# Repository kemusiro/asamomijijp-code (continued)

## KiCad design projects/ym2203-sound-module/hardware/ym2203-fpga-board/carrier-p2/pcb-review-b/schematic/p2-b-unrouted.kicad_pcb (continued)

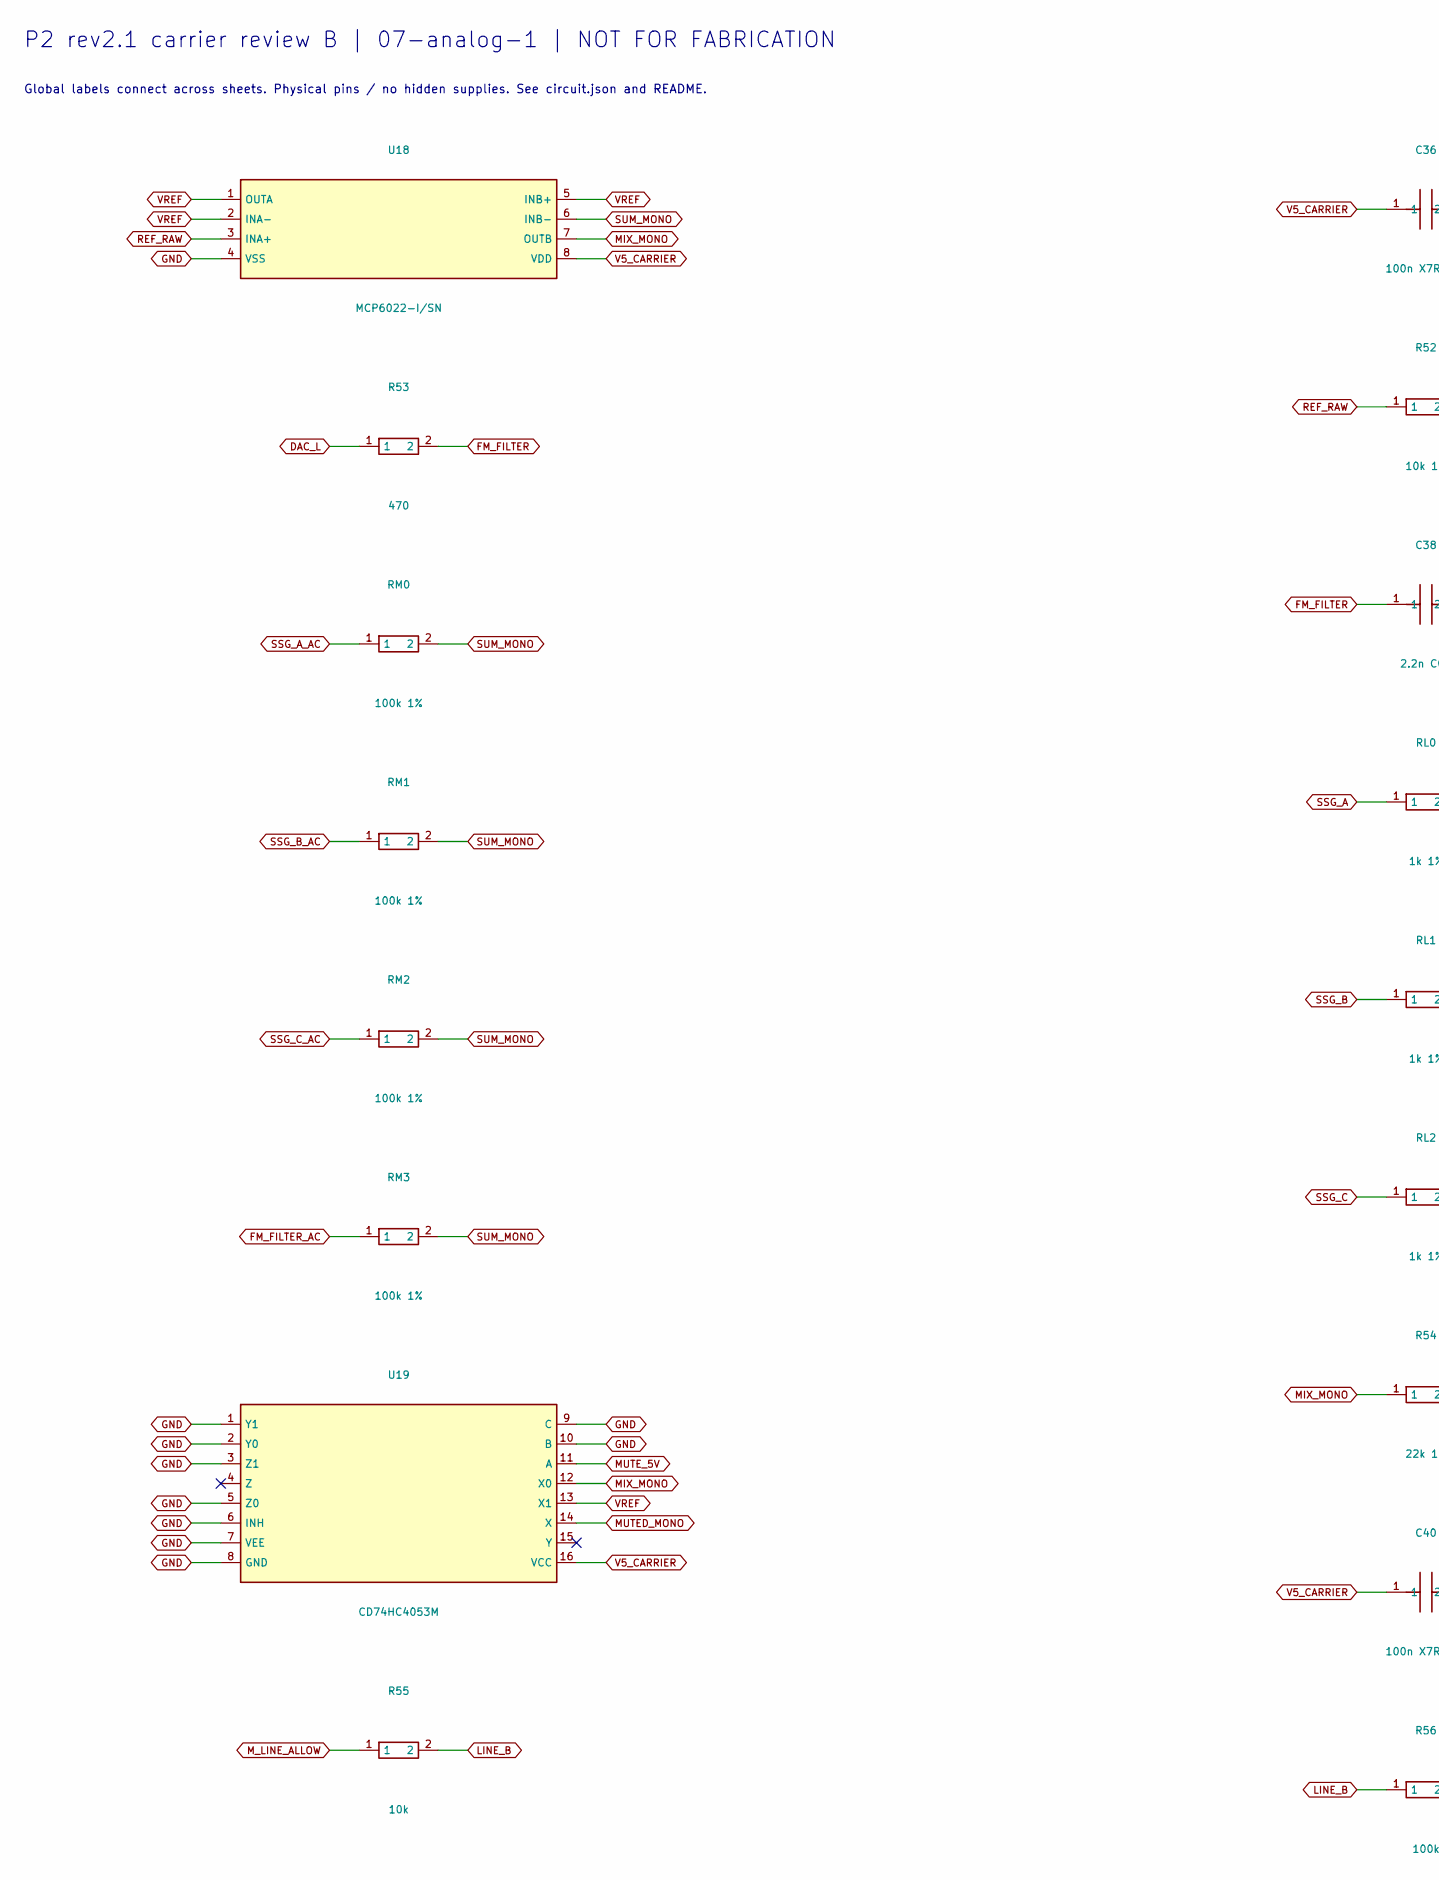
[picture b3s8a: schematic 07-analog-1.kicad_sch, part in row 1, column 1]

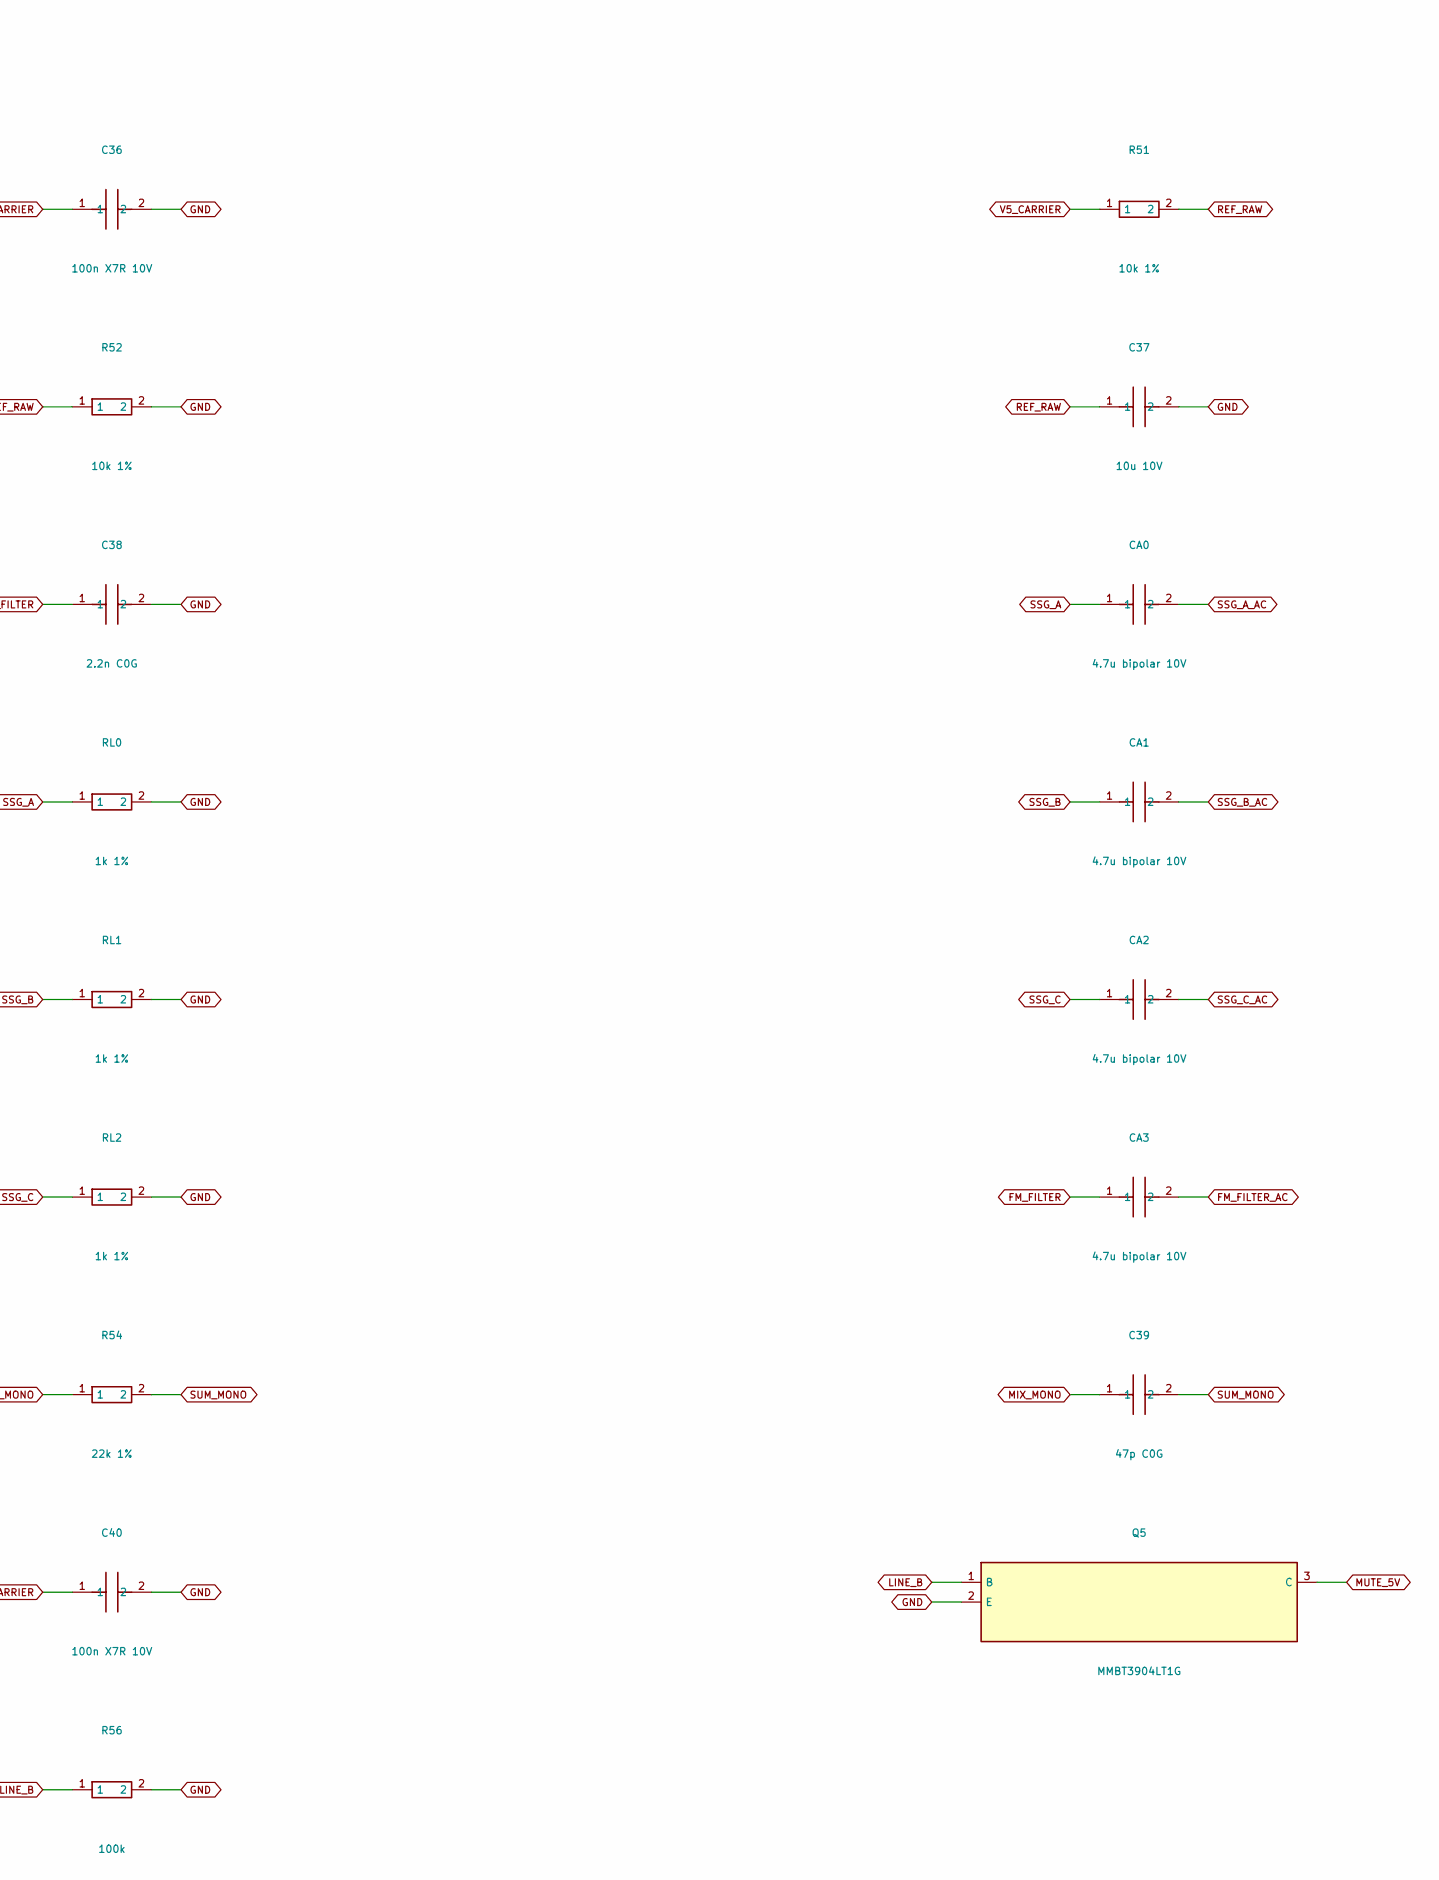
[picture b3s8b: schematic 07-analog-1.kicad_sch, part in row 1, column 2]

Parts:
C36, C40: 100n X7R 10V; C_0805_2012Metric
C37: 10u 10V; C_0805_2012Metric
C38: 2.2n C0G; C_0805_2012Metric
C39: 47p C0G; C_0805_2012Metric
CA0, CA1, CA2, CA3: 4.7u bipolar 10V; C_Radial_D5.0mm_H11.0mm_P2.00mm
Q5: MMBT3904LT1G; SOT-23
R51, R52: 10k 1%; R_0805_2012Metric
R53: 470; R_0805_2012Metric
R54: 22k 1%; R_0805_2012Metric
R55: 10k; R_0805_2012Metric
R56: 100k; R_0805_2012Metric
RL0, RL1, RL2: 1k 1%; R_0805_2012Metric
RM0, RM1, RM2, RM3: 100k 1%; R_0805_2012Metric
U18: MCP6022-I/SN; SOIC-8_3.9x4.9mm_P1.27mm
U19: CD74HC4053M; SOIC-16_3.9x9.9mm_P1.27mm

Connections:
DAC_L: R53.1; also elsewhere on the board
FM_FILTER: C38.1, CA3.1, R53.2
FM_FILTER_AC: CA3.2, RM3.1
GND: C36.2, C37.2, C38.2, C40.2, Q5.2 (E), R52.2, R56.2, RL0.2, RL1.2, RL2.2, U18.4 (VSS), U19.1 (Y1), U19.2 (Y0), U19.3 (Z1), U19.5 (Z0), U19.6 (INH), U19.7 (VEE), U19.8 (GND), U19.9 (C), U19.10 (B); also elsewhere on the board
LINE_B: Q5.1 (B), R55.2, R56.1
MIX_MONO: C39.1, R54.1, U18.7 (OUTB), U19.12 (X0)
MUTED_MONO: U19.14 (X); also elsewhere on the board
MUTE_5V: Q5.3 (C), U19.11 (A); also elsewhere on the board
M_LINE_ALLOW: R55.1; also elsewhere on the board
REF_RAW: C37.1, R51.2, R52.1, U18.3 (INA+)
SSG_A: CA0.1, RL0.1; also elsewhere on the board
SSG_A_AC: CA0.2, RM0.1
SSG_B: CA1.1, RL1.1; also elsewhere on the board
SSG_B_AC: CA1.2, RM1.1
SSG_C: CA2.1, RL2.1; also elsewhere on the board
SSG_C_AC: CA2.2, RM2.1
SUM_MONO: C39.2, R54.2, RM0.2, RM1.2, RM2.2, RM3.2, U18.6 (INB-)
V5_CARRIER: C36.1, C40.1, R51.1, U18.8 (VDD), U19.16 (VCC); also elsewhere on the board
VREF: U18.1 (OUTA), U18.2 (INA-), U18.5 (INB+), U19.13 (X1)

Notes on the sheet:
P2 rev2.1 carrier review B | 07-analog-1 | NOT FOR FABRICATION
Global labels connect across sheets. Physical pins / no hidden supplies. See circuit.json and README.

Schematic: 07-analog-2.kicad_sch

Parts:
C41: 4.7u bipolar 10V; C_Radial_D5.0mm_H11.0mm_P2.00mm
JLINE: JLINE; PinHeader_1x03_P2.54mm_Vertical
JPOT: JPOT; PinHeader_1x06_P2.54mm_Vertical
R57: 10k; R_0805_2012Metric
R58: 100k; R_0805_2012Metric
R59, R60: 100; R_0805_2012Metric

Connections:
GND: JLINE.2, JPOT.1, JPOT.4, R58.2; also elsewhere on the board
LINE_L: JLINE.1, R59.2
LINE_R: JLINE.3, R60.2
MUTED_MONO: C41.1; also elsewhere on the board
MUTE_5V: R57.2; also elsewhere on the board
OUT_AC: C41.2, JPOT.3, JPOT.6, R58.1
V5_CARRIER: R57.1; also elsewhere on the board
VOL_L: JPOT.2, R59.1
VOL_R: JPOT.5, R60.1

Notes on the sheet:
P2 rev2.1 carrier review B | 07-analog-2 | NOT FOR FABRICATION
Global labels connect across sheets. Physical pins / no hidden supplies. See circuit.json and README.

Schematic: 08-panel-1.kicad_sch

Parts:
CPANEL: 100n X7R 10V; C_0805_2012Metric
DLED0: RX GREEN; LED_D3.0mm
DLED1: FM1; LED_D3.0mm
DLED2: FM2; LED_D3.0mm
DLED3: FM3; LED_D3.0mm
DLED4: SSGA; LED_D3.0mm
DLED5: SSGB; LED_D3.0mm
RLED0, RLED1, RLED2, RLED3, RLED4, RLED5, RLED6: 1k; R_0805_2012Metric
RP0, RP1, RP2, RP3, RP4, RP5: 10k; R_0805_2012Metric
SWCLOCK: 4-bit DIP ON=0 SW1=LSB; SW_DIP_SPSTx04_Slide_6.7x11.72mm_W7.62mm_P2.54mm_LowProfile
SWSTOP: STOP; SW_PUSH_6mm_H4.3mm
SWTEST: TEST; SW_PUSH_6mm_H4.3mm
UPANEL: MCP23017-E/SO; SOIC-28W_7.5x17.9mm_P1.27mm

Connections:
DIP1_N: RP0.2, SWCLOCK.1 (SW1), UPANEL.21 (GPA0)
DIP2_N: RP1.2, SWCLOCK.2 (SW2), UPANEL.22 (GPA1)
DIP3_N: RP2.2, SWCLOCK.3 (SW3), UPANEL.23 (GPA2)
DIP4_N: RP3.2, SWCLOCK.4 (SW4), UPANEL.24 (GPA3)
FM1_LED_N: DLED1.1 (K), UPANEL.1 (GPB0)
FM2_LED_N: DLED2.1 (K), UPANEL.2 (GPB1)
FM3_LED_N: DLED3.1 (K), UPANEL.3 (GPB2)
GND: CPANEL.2, SWCLOCK.5 (GND), SWCLOCK.6 (GND), SWCLOCK.7 (GND), SWCLOCK.8 (GND), SWSTOP.2 (B), SWTEST.2 (B), UPANEL.10 (VSS), UPANEL.15 (A0), UPANEL.16 (A1), UPANEL.17 (A2); also elsewhere on the board
LED_ANODE0: DLED0.2 (A), RLED0.1
LED_ANODE1: DLED1.2 (A), RLED1.1
LED_ANODE2: DLED2.2 (A), RLED2.1
LED_ANODE3: DLED3.2 (A), RLED3.1
LED_ANODE4: DLED4.2 (A), RLED4.1
LED_ANODE5: DLED5.2 (A), RLED5.1
LED_ANODE6: RLED6.1; also elsewhere on the board
PANEL_SCL: UPANEL.12 (SCL); also elsewhere on the board
PANEL_SDA: UPANEL.13 (SDA); also elsewhere on the board
RUN_N: UPANEL.18 (RESETn); also elsewhere on the board
RX_LED_N: DLED0.1 (K), UPANEL.28 (GPA7)
SSGA_LED_N: DLED4.1 (K), UPANEL.4 (GPB3)
SSGB_LED_N: DLED5.1 (K), UPANEL.5 (GPB4)
SSGC_LED_N: UPANEL.6 (GPB5); also elsewhere on the board
STOP_N: RP4.2, SWSTOP.1 (A), UPANEL.25 (GPA4)
TEST_N: RP5.2, SWTEST.1 (A), UPANEL.26 (GPA5)
V3V3: CPANEL.1, RLED0.2, RLED1.2, RLED2.2, RLED3.2, RLED4.2, RLED5.2, RLED6.2, RP0.1, RP1.1, RP2.1, RP3.1, RP4.1, RP5.1, UPANEL.9 (VDD); also elsewhere on the board

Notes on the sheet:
P2 rev2.1 carrier review B | 08-panel-1 | NOT FOR FABRICATION
Global labels connect across sheets. Physical pins / no hidden supplies. See circuit.json and README.

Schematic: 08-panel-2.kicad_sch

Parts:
DLED6: SSGC; LED_D3.0mm

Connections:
LED_ANODE6: DLED6.2 (A); also elsewhere on the board
SSGC_LED_N: DLED6.1 (K); also elsewhere on the board

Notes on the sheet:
P2 rev2.1 carrier review B | 08-panel-2 | NOT FOR FABRICATION
Global labels connect across sheets. Physical pins / no hidden supplies. See circuit.json and README.

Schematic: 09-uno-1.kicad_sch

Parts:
JP5V: OPEN DEFAULT / SHIELD POWER; SolderJumper-2_P1.3mm_Open_RoundedPad1.0x1.5mm
JP_SCL: CLOSED I2C / OPEN ADC (STOPPED); SolderJumper-2_P1.3mm_Bridged_RoundedPad1.0x1.5mm
JP_SDA: CLOSED I2C / OPEN ADC (STOPPED); SolderJumper-2_P1.3mm_Bridged_RoundedPad1.0x1.5mm
JUNO_A: JUNO_A 3V3 ONLY; JUNO_A
JUNO_D0: JUNO_D0 3V3 ONLY; JUNO_D0
JUNO_D8: JUNO_D8 3V3 ONLY; JUNO_D8
JUNO_PWR: JUNO_PWR 3V3 ONLY; JUNO_PWR
JUNO_SPI: JUNO_SPI 3V3 ONLY; JUNO_SPI

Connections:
EXT_A0: JUNO_A.1 (A0); also elsewhere on the board
EXT_A1: JUNO_A.2 (A1); also elsewhere on the board
EXT_A2: JUNO_A.3 (A2); also elsewhere on the board
EXT_A3: JUNO_A.4 (A3); also elsewhere on the board
EXT_A4: JP_SDA.1 (MCU_HEADER), JUNO_A.5 (A4), JUNO_D8.9 (SDA); also elsewhere on the board
EXT_A5: JP_SCL.1 (MCU_HEADER), JUNO_A.6 (A5), JUNO_D8.10 (SCL); also elsewhere on the board
EXT_D0: JUNO_D0.1 (D0); also elsewhere on the board
EXT_D1: JUNO_D0.2 (D1); also elsewhere on the board
EXT_D2: JUNO_D0.3 (D2); also elsewhere on the board
EXT_D3: JUNO_D0.4 (D3); also elsewhere on the board
EXT_D4: JUNO_D0.5 (D4); also elsewhere on the board
EXT_D5: JUNO_D0.6 (D5); also elsewhere on the board
EXT_D6: JUNO_D0.7 (D6); also elsewhere on the board
EXT_D7: JUNO_D0.8 (D7); also elsewhere on the board
EXT_D8: JUNO_D8.1 (D8); also elsewhere on the board
EXT_D9: JUNO_D8.2 (D9); also elsewhere on the board
EXT_D10: JUNO_D8.3 (D10); also elsewhere on the board
EXT_D11: JUNO_D8.4 (D11), JUNO_SPI.4 (COPI); also elsewhere on the board
EXT_D12: JUNO_D8.5 (D12), JUNO_SPI.1 (CIPO); also elsewhere on the board
EXT_D13: JUNO_D8.6 (D13), JUNO_SPI.3 (SCK); also elsewhere on the board
GND: JUNO_D8.7 (GND), JUNO_PWR.6 (GND), JUNO_PWR.7 (GND), JUNO_SPI.6 (GND); also elsewhere on the board
PANEL_SCL: JP_SCL.2 (BOARD_I2C); also elsewhere on the board
PANEL_SDA: JP_SDA.2 (BOARD_I2C); also elsewhere on the board
RUN_N: JUNO_PWR.3 (RESET), JUNO_SPI.5 (RESET); also elsewhere on the board
SHIELD_5V: JP5V.2 (SHIELD), JUNO_PWR.5 (5V)
V3V3: JUNO_PWR.2 (IOREF), JUNO_SPI.2 (VCC_3V3); also elsewhere on the board
V3_AUX: JUNO_PWR.4 (3V3); also elsewhere on the board
V5_CARRIER: JP5V.1 (5V); also elsewhere on the board

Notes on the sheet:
P2 rev2.1 carrier review B | 09-uno-1 | NOT FOR FABRICATION
Global labels connect across sheets. Physical pins / no hidden supplies. See circuit.json and README.

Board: 4 copper layers, 172 parts (0 on the bottom side), 137 nets, no tracks yet.

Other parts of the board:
H1, H2, H3, H4, H5, H6, H7, H8: MountingHole_3.2mm_M3

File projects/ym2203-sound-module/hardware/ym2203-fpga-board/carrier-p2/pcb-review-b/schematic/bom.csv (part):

Reference,Value,Footprint,Sheet,Datasheet,Review note
MPGA,PGA2350 PIM722 SOCKET,P2C:PGA2350_Socket_64,01-module,https://shop.pimoroni.com/products/pga2350,Top view A1 at upper left. GP47 B8 NC: PSRAM onboard. USB 27R4 ALREADY on module. ADC_VREF/3V3_EN NC.
JHOST,JHOST,Connector_PinHeader_2.54mm:PinHeader_1x04_P2.54mm_Vertical,01-module,,Existing OTHER Pico GP0 SDA / GP1 SCL; 100kHz / 0x42; NO supply pin
JSWD,JSWD,Connector_PinHeader_2.54mm:PinHeader_1x03_P2.54mm_Vertical,01-module,,3.3V SWD probe; never power carrier through probe
SWRESET,RESET,Button_Switch_THT:SW_PUSH_6mm_H4.3mm,01-module,,Two contact numbers; each has two duplicated physical pads in KiCad footprint
SWBOOT,BOOTSEL,Button_Switch_THT:SW_PUSH_6mm_H4.3mm,01-module,,Two contact numbers; each has two duplicated physical pads in KiCad footprint
RRUN,10k,Resistor_SMD:R_0805_2012Metric,01-module,,
CRUN,1n C0G,Capacitor_SMD:C_0805_2012Metric,01-module,,Capacitor body/height and effective capacitance to be checked against final MPN
JPOWER,JPOWER,Connector_PinHeader_2.54mm:PinHeader_1x02_P2.54mm_Vertical,02-power-usb,,Regulated external5V; 1.5A supply target; verify 4.95..5.05V at YM under load
F1,PTC 1.1A hold,Fuse:Fuse_1812_4532Metric,02-power-usb,,
C1,100u 10V,Capacitor_THT:CP_Radial_D6.3mm_P2.50mm,02-power-usb,,Capacitor body/height and effective capacitance to be checked against final MPN
C2,10u 10V,Capacitor_SMD:C_0805_2012Metric,02-power-usb,,Capacitor body/height and effective capacitance to be checked against final MPN
JUSB,HRO TYPE-C-31-M-12 USB2 DEVICE,Connector_USB:USB_C_Receptacle_HRO_TYPE-C-31-M-12,02-power-usb,http://www.krhro.com/uploads/soft/180320/1-1P320120243.pdf,Self-powered. A6/B6 DP; A7/B7 DM; SBU NC. Verify exact purchased connector drawing before layout release.
RCC1,5.1k 1%,Resistor_SMD:R_0805_2012Metric,02-power-usb,,
RCC2,5.1k 1%,Resistor_SMD:R_0805_2012Metric,02-power-usb,,
UESD,USBLC6-2SC6,Package_TO_SOT_SMD:SOT-23-6,02-power-usb,https://www.st.com/resource/en/datasheet/usblc6-2.pdf,"Place at USB connector, short return. VBUS protection/sense only; no external5V power path."
CVBUS,100n X7R 10V,Capacitor_SMD:C_0805_2012Metric,02-power-usb,,Capacitor body/height and effective capacitance to be checked against final MPN
RVB1,47k 0.1%,Resistor_SMD:R_0805_2012Metric,02-power-usb,,
RVB2,68k 0.1%,Resistor_SMD:R_0805_2012Metric,02-power-usb,,
CVBD,100p C0G,Capacitor_SMD:C_0805_2012Metric,02-power-usb,,Capacitor body/height and effective capacitance to be checked against final MPN
UVBUS,SN74LVC1G17DBVR,Package_TO_SOT_SMD:SOT-23-5,02-power-usb,https://www.ti.com/lit/ds/symlink/sn74lvc1g17.pdf,Schmitt buffer / Ioff; USB VBUS sense to GP46; no power through USB
CVB3,100n X7R 10V,Capacitor_SMD:C_0805_2012Metric,02-power-usb,,Capacitor body/height and effective capacitance to be checked against final MPN
RVB3,100k,Resistor_SMD:R_0805_2012Metric,02-power-usb,,
Q1,MMBT3904LT1G,Package_TO_SOT_SMD:SOT-23,03-default-stop,https://www.onsemi.com/pdf/datasheet/mmbt3904lt1-d.pdf,
R19,4.7k,Resistor_SMD:R_0805_2012Metric,03-default-stop,,
Q2,MMBT3904LT1G,Package_TO_SOT_SMD:SOT-23,03-default-stop,https://www.onsemi.com/pdf/datasheet/mmbt3904lt1-d.pdf,
R20,10k,Resistor_SMD:R_0805_2012Metric,03-default-stop,,
R21,100k,Resistor_SMD:R_0805_2012Metric,03-default-stop,,
R22,10k,Resistor_SMD:R_0805_2012Metric,03-default-stop,,
R23,100k,Resistor_SMD:R_0805_2012Metric,03-default-stop,,
RPDAC,10k,Resistor_SMD:R_0805_2012Metric,03-default-stop,,
RPLINE,10k,Resistor_SMD:R_0805_2012Metric,03-default-stop,,
U8,SN74LVC8T245PWR,Package_SO:TSSOP-24_4.4x7.8mm_P0.65mm,04-ym-bus,https://www.ti.com/lit/ds/symlink/sn74lvc8t245.pdf,Bare IC pinout: OE=22 DIR=2; NOT the Rev C breakout numbering
U9,SN74LVC8T245PWR,Package_SO:TSSOP-24_4.4x7.8mm_P0.65mm,04-ym-bus,https://www.ti.com/lit/ds/symlink/sn74lvc8t245.pdf,Bare IC pinout: OE=22 DIR=2; NOT the Rev C breakout numbering
C11,100n X7R 10V,Capacitor_SMD:C_0805_2012Metric,04-ym-bus,,Capacitor body/height and effective capacitance to be checked against final MPN
C12,100n X7R 10V,Capacitor_SMD:C_0805_2012Metric,04-ym-bus,,Capacitor body/height and effective capacitance to be checked against final MPN
C13,100n X7R 10V,Capacitor_SMD:C_0805_2012Metric,04-ym-bus,,Capacitor body/height and effective capacitance to be checked against final MPN
C14,100n X7R 10V,Capacitor_SMD:C_0805_2012Metric,04-ym-bus,,Capacitor body/height and effective capacitance to be checked against final MPN
C15,100n X7R 10V,Capacitor_SMD:C_0805_2012Metric,04-ym-bus,,Capacitor body/height and effective capacitance to be checked against final MPN
C16,100n X7R 10V,Capacitor_SMD:C_0805_2012Metric,04-ym-bus,,Capacitor body/height and effective capacitance to be checked against final MPN
RDIR,10k,Resistor_SMD:R_0805_2012Metric,04-ym-bus,,
RDOE,10k,Resistor_SMD:R_0805_2012Metric,04-ym-bus,,
RCOE,10k,Resistor_SMD:R_0805_2012Metric,04-ym-bus,,
RD0,100k,Resistor_SMD:R_0805_2012Metric,04-ym-bus,,
RD1,100k,Resistor_SMD:R_0805_2012Metric,04-ym-bus,,
RD2,100k,Resistor_SMD:R_0805_2012Metric,04-ym-bus,,
RD3,100k,Resistor_SMD:R_0805_2012Metric,04-ym-bus,,
RD4,100k,Resistor_SMD:R_0805_2012Metric,04-ym-bus,,
RD5,100k,Resistor_SMD:R_0805_2012Metric,04-ym-bus,,
RD6,100k,Resistor_SMD:R_0805_2012Metric,04-ym-bus,,
RD7,100k,Resistor_SMD:R_0805_2012Metric,04-ym-bus,,
R32,10k,Resistor_SMD:R_0805_2012Metric,04-ym-bus,,
RMC32,10k,Resistor_SMD:R_0805_2012Metric,04-ym-bus,,
R33,10k,Resistor_SMD:R_0805_2012Metric,04-ym-bus,,
RMC33,10k,Resistor_SMD:R_0805_2012Metric,04-ym-bus,,
R34,10k,Resistor_SMD:R_0805_2012Metric,04-ym-bus,,
RMC34,10k,Resistor_SMD:R_0805_2012Metric,04-ym-bus,,
R35,100k,Resistor_SMD:R_0805_2012Metric,04-ym-bus,,
RMA,100k,Resistor_SMD:R_0805_2012Metric,04-ym-bus,,
U12,YM2203C SOCKET,Package_DIP:DIP-40_W15.24mm_Socket,05-clock-ym,https://www.bitsavers.org/components/yamaha/YM2203_198911.pdf,IO ports A/B unused; IRQ unconnected; 5V supply
C19,100n X7R 10V,Capacitor_SMD:C_0805_2012Metric,05-clock-ym,,Capacitor body/height and effective capacitance to be checked against final MPN
C20,10u 10V,Capacitor_SMD:C_0805_2012Metric,05-clock-ym,,Capacitor body/height and effective capacitance to be checked against final MPN
U13,Si5351A-B-GT,Package_SO:MSOP-10_3x3mm_P0.5mm,05-clock-ym,https://www.skyworksinc.com/-/media/SkyWorks/SL/documents/pu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,Blank no-boot preset; P2 firmware must disable CLK1/2 and configure CLK0 before reset release
Y1,25MHz CL10pF +/-20ppm,Crystal:Crystal_SMD_3225-4Pin_3.2x2.5mm,05-clock-ym,,ABM8-25.000MHZ-10-1-U-T candidate; ESR/drive and actual footprint need confirmation
C21,100n X7R 10V,Capacitor_SMD:C_0805_2012Metric,05-clock-ym,,Capacitor body/height and effective capacitance to be checked against final MPN
C22,100n X7R 10V,Capacitor_SMD:C_0805_2012Metric,05-clock-ym,,Capacitor body/height and effective capacitance to be checked against final MPN
R37,2.2k,Resistor_SMD:R_0805_2012Metric,05-clock-ym,,
R38,2.2k,Resistor_SMD:R_0805_2012Metric,05-clock-ym,,
U14,SN74LVC1T45DBVR,Package_TO_SOT_SMD:SOT-23-6,05-clock-ym,https://www.ti.com/lit/ds/symlink/sn74lvc1t45.pdf,Fixed A->B; clock may run while YM RESET is asserted
C23,100n X7R 10V,Capacitor_SMD:C_0805_2012Metric,05-clock-ym,,Capacitor body/height and effective capacitance to be checked against final MPN
C24,100n X7R 10V,Capacitor_SMD:C_0805_2012Metric,05-clock-ym,,Capacitor body/height and effective capacitance to be checked against final MPN
R39,33,Resistor_SMD:R_0805_2012Metric,05-clock-ym,,
R40,100k,Resistor_SMD:R_0805_2012Metric,05-clock-ym,,
U16,SN74LVC125APWR,Package_SO:TSSOP-14_4.4x5mm_P0.65mm,06-dac,https://www.ti.com/lit/ds/symlink/sn74lvc125a.pdf,
C27,100n X7R 10V,Capacitor_SMD:C_0805_2012Metric,06-dac,,Capacitor body/height and effective capacitance to be checked against final MPN
R42,100k,Resistor_SMD:R_0805_2012Metric,06-dac,,
R43,100k,Resistor_SMD:R_0805_2012Metric,06-dac,,
R44,100k,Resistor_SMD:R_0805_2012Metric,06-dac,,
R45,2.2k,Resistor_SMD:R_0805_2012Metric,06-dac,,
R46,2.2k,Resistor_SMD:R_0805_2012Metric,06-dac,,
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
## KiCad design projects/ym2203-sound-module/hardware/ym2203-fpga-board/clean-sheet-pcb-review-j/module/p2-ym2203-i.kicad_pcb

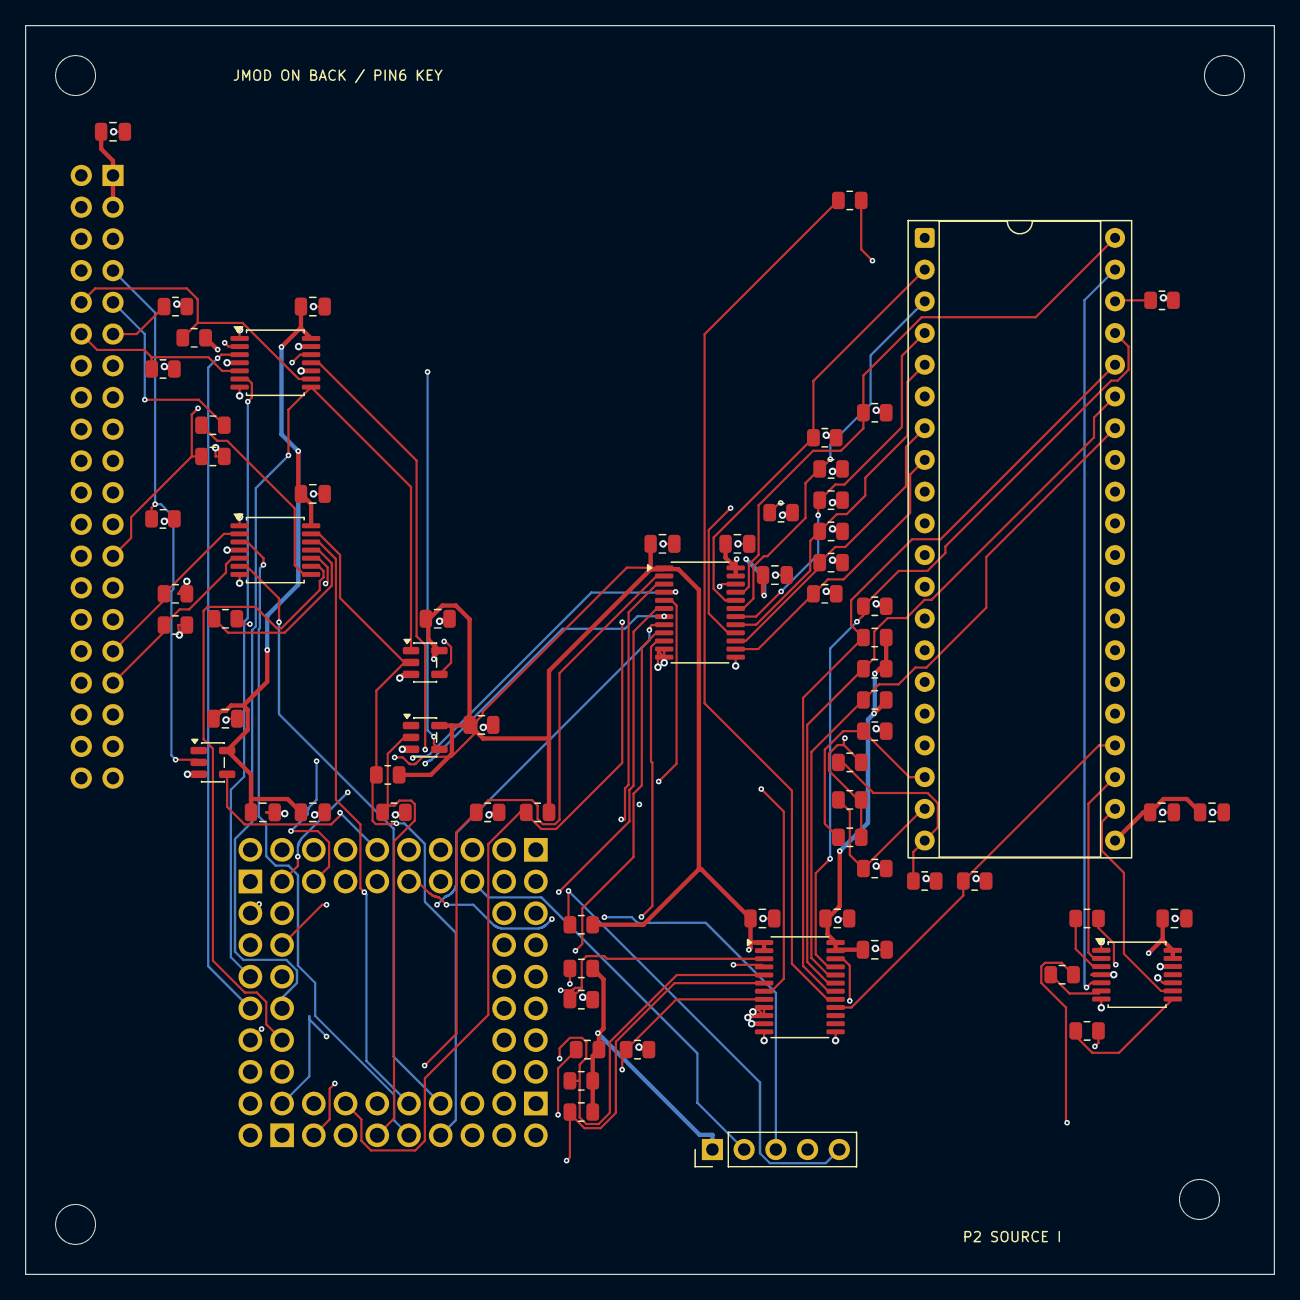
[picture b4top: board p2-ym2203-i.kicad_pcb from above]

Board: 4 copper layers, 100.0 x 100.0 mm, 80 parts (1 on the bottom side), 73 nets.

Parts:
C11, C12, C13, C14, C15, C16, C19, C27: 100n X7R 10V; C_0805_2012Metric
C20: 10u 10V; C_0805_2012Metric
CCORE: 100n X7R 10V; C_0805_2012Metric
CCOREB: 4.7u X7R 10V; C_0805_2012Metric
CMOD5: 22u X7R 10V; C_0805_2012Metric
CUALERT: 100n X7R 10V; C_0805_2012Metric
CULINK0, CULINK1: 100n X7R 10V; C_0805_2012Metric
CURUNOD: 100n X7R 10V; C_0805_2012Metric
CUTXOR: 100n X7R 10V; C_0805_2012Metric
H1, H2, H3, H4: MountingHole_3.2mm_M3
JCORE1: Core2350B0 P1 / individual receptacles; Core2350B0_P1_IndividualSockets
JCORE2: Core2350B0 P2 / individual receptacles; Core2350B0_P2_IndividualSockets
JCORE3: Core2350B0 P3 / individual receptacles; Core2350B0_P3_IndividualSockets
JCORE4: Core2350B0 P4 / individual receptacles; Core2350B0_P4_IndividualSockets
JMOD: P2 G40 / KEY6 / NO LEGACY MATE; PinHeader_2x20_P2.54mm_Vertical
JSWD: Core SWD / VREF sense only; PinHeader_1x05_P2.54mm_Vertical
R32, R33, R34: 10k; R_0805_2012Metric
R35, R40: 100k; R_0805_2012Metric
R39: 33; R_0805_2012Metric
RCOE: 10k; R_0805_2012Metric
RD0, RD1, RD2, RD3, RD4, RD5, RD6, RD7: 100k; R_0805_2012Metric
RDIR: 10k; R_0805_2012Metric
RDOE: 10k; R_0805_2012Metric
RENPD: 10k; R_0805_2012Metric
RL0, RL1, RL2: 1.33k 1%; R_0805_2012Metric
RMA: 100k; R_0805_2012Metric
RMADR: 100k; R_0805_2012Metric
RMBCK: 100k; R_0805_2012Metric
RMC32, RMC33, RMC34: 10k; R_0805_2012Metric
RMCLK: 100k; R_0805_2012Metric
RMCS: 10k; R_0805_2012Metric
RMLR: 100k; R_0805_2012Metric
RMMOSI: 100k; R_0805_2012Metric
RMSCK: 100k; R_0805_2012Metric
RMTXDATA: 33; R_0805_2012Metric
RMTXMISO: 33; R_0805_2012Metric
RRELDEFAULT: 100k; R_0805_2012Metric
RRUNUP: 10k; R_0805_2012Metric
RS3, RS6, RS8: 33; R_0805_2012Metric
RSMIXA: 10k 1%; R_0805_2012Metric
RSMIXB: 10k 1%; R_0805_2012Metric
RSMIXC: 10k 1%; R_0805_2012Metric
RTXDIS: 10k; R_0805_2012Metric
RYMRESET: 10k; R_0805_2012Metric
U8, U9: SN74LVC8T245PWR; TSSOP-24_4.4x7.8mm_P0.65mm
U12: YM2203C SOCKET; DIP-40_W15.24mm_Socket
U16: SN74LV4T125PWR; TSSOP-14_4.4x5mm_P0.65mm
UALERT: SN74LVC1G07DBVR; SOT-23-5
ULINK0, ULINK1: SN74LV4T125PWR; TSSOP-14_4.4x5mm_P0.65mm
URUNOD: SN74LVC1G07DBVR; SOT-23-5
UTXOR: SN74LVC1G32DBVR; SOT-23-5

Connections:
AUDIO_L: JMOD.37, RSMIXA.2, RSMIXB.2, RSMIXC.2
BUF_M_FM_CLK: RS6.1, U16.6
BUF_M_FM_SD: RS3.1, U16.3
BUF_M_FM_SH: RS8.1, U16.8
CORE_RUN_N: JCORE2.11, JSWD.5, RRUNUP.1, URUNOD.4
CORE_SWCLK: JCORE2.10, JSWD.3
CORE_SWD: JCORE2.6, JSWD.2
GND: C11.2, C12.2, C13.2, C14.2, C15.2, C16.2, C19.2, C20.2, C27.2, CCORE.2, CCOREB.2, CMOD5.2, CUALERT.2, CULINK0.2, CULINK1.2, CURUNOD.2, CUTXOR.2, JCORE1.15, JCORE2.1, JCORE2.8, JCORE2.14, JCORE3.15, JCORE4.15, JMOD.2, JMOD.4, JMOD.13, JMOD.14, JMOD.26, JMOD.28, JMOD.30, JMOD.32, JMOD.35, JMOD.36, JMOD.38, JMOD.40, JSWD.4, R35.2, R40.2, RD0.2, RD1.2, RD2.2, RD3.2, RD4.2, RD5.2, RD6.2, RD7.2, RDIR.2, RENPD.2, RL0.2, RL1.2, RL2.2, RMA.2, RMADR.2, RMBCK.2, RMCLK.2, RMLR.2, RMMOSI.2, RMSCK.2, RRELDEFAULT.2, RYMRESET.2, U8.11, U8.12, U8.13, U9.9, U9.10, U9.11, U9.12, U9.13, U12.1, U12.17, U16.1, U16.4, U16.7, U16.10, U16.12, UALERT.3, ULINK0.1, ULINK0.4, ULINK0.7, ULINK0.10, ULINK0.13, ULINK1.1, ULINK1.4, ULINK1.7, URUNOD.3, UTXOR.3
LINK_TX_DATA: RMTXDATA.1, ULINK1.11
LINK_TX_DISABLE: JCORE3.11, RTXDIS.1, ULINK1.13, UTXOR.2
LINK_TX_MISO: RMTXMISO.1, ULINK1.8
L_BUS_D0: JMOD.9, RMTXMISO.2
L_BUS_D1: JMOD.10, RMCS.1, ULINK0.9
L_BUS_D2: JMOD.11, RMSCK.1, ULINK0.2
L_BUS_D3: JMOD.12, RMMOSI.1, ULINK0.5
L_MOD_ALERT_N: JMOD.8, UALERT.4
L_MOD_ENABLE: JMOD.7, RENPD.1, URUNOD.2
L_MOD_I2S_BCK: JMOD.31, RMBCK.1, ULINK1.2
L_MOD_I2S_DATA: JMOD.34, RMTXDATA.2
L_MOD_I2S_LRCK: JMOD.33, RMLR.1, ULINK1.5
L_SOUND_CLK0: JMOD.25, RMCLK.1, ULINK0.12
MCU_3V3: C11.1, C14.1, C27.1, CCORE.1, CCOREB.1, CUALERT.1, CULINK0.1, CULINK1.1, CURUNOD.1, CUTXOR.1, JCORE2.16, JSWD.1, RCOE.2, RDOE.2, RMC32.2, RMC33.2, RMC34.2, RMCS.2, RRUNUP.2, RTXDIS.2, U8.1, U9.1, U9.2, U16.13, U16.14, UALERT.5, ULINK0.14, ULINK1.14, URUNOD.5, UTXOR.5
MISO_OE_N: ULINK1.10, UTXOR.4
MOD_ALERT_DRIVE: JCORE3.7, RMADR.1, UALERT.2
MOD_I2S_BCK: JCORE3.9, ULINK1.3
MOD_I2S_DATA: JCORE3.12, ULINK1.12
MOD_I2S_LRCK: JCORE3.14, ULINK1.6
MOD_SPI_CS_N: JCORE1.12, ULINK0.8, UTXOR.1
MOD_SPI_MISO: JCORE1.14, ULINK1.9
MOD_SPI_MOSI: JCORE1.7, ULINK0.6
MOD_SPI_SCK: JCORE1.9, ULINK0.3
SSG_A: RL0.1, RSMIXA.1, U12.20
SSG_B: RL1.1, RSMIXB.1, U12.19
SSG_C: RL2.1, RSMIXC.1, U12.18
V5_MODULE: C12.1, C13.1, C15.1, C16.1, C19.1, C20.1, CMOD5.1, JCORE2.15, JMOD.1, JMOD.3, R32.2, R33.2, R34.2, U8.23, U8.24, U9.23, U9.24, U12.21
YM_A0: JCORE1.11, RMA.1, U9.3
YM_CLK_5: R39.1, U9.17
YM_CLOCK_3V3: U9.7, ULINK0.11
YM_CS_N: JCORE1.16, RMC32.1, U9.4
YM_CTRL_OE_N: JCORE3.5, RCOE.1, U9.22
YM_D0: JCORE1.2, U8.3
YM_D1: JCORE1.4, U8.4
YM_D2: JCORE1.1, U8.5
YM_D3: JCORE1.6, U8.6
YM_D4: JCORE1.3, U8.7
YM_D5: JCORE1.8, U8.8
YM_D6: JCORE1.5, U8.9
YM_D7: JCORE1.10, U8.10
YM_DATA_DIR: JCORE3.3, RDIR.1, U8.2
YM_DATA_OE_N: JCORE3.8, RDOE.1, U8.22
YM_FM_CLK: JCORE3.1, RS6.2
YM_FM_SD: JCORE3.4, RS3.2
YM_FM_SH: JCORE3.6, RS8.2
YM_RD_N: JCORE3.2, RMC34.1, U9.6
YM_RESET_RELEASE: JCORE3.10, RRELDEFAULT.1, U9.8
YM_WR_N: JCORE1.13, RMC33.1, U9.5
Y_A0: R35.1, U9.21, U12.37
Y_CLK: U12.39, U16.5
Y_CS_N: R32.1, U9.20, U12.34
Y_D0: RD0.1, U8.21, U12.40
Y_D1: RD1.1, U8.20, U12.2
Y_D2: RD2.1, U8.19, U12.3
Y_D3: RD3.1, U8.18, U12.4
Y_D4: RD4.1, U8.17, U12.5
Y_D5: RD5.1, U8.16, U12.6
Y_D6: RD6.1, U8.15, U12.7
Y_D7: RD7.1, U8.14, U12.8
Y_PHI_M: R39.2, R40.1, U12.38
Y_RD_N: R34.1, U9.18, U12.36
Y_RESET_N: RYMRESET.1, U9.16, U12.24
Y_SD: U12.23, U16.2
Y_SH: U12.22, U16.9
Y_WR_N: R33.1, U9.19, U12.35
